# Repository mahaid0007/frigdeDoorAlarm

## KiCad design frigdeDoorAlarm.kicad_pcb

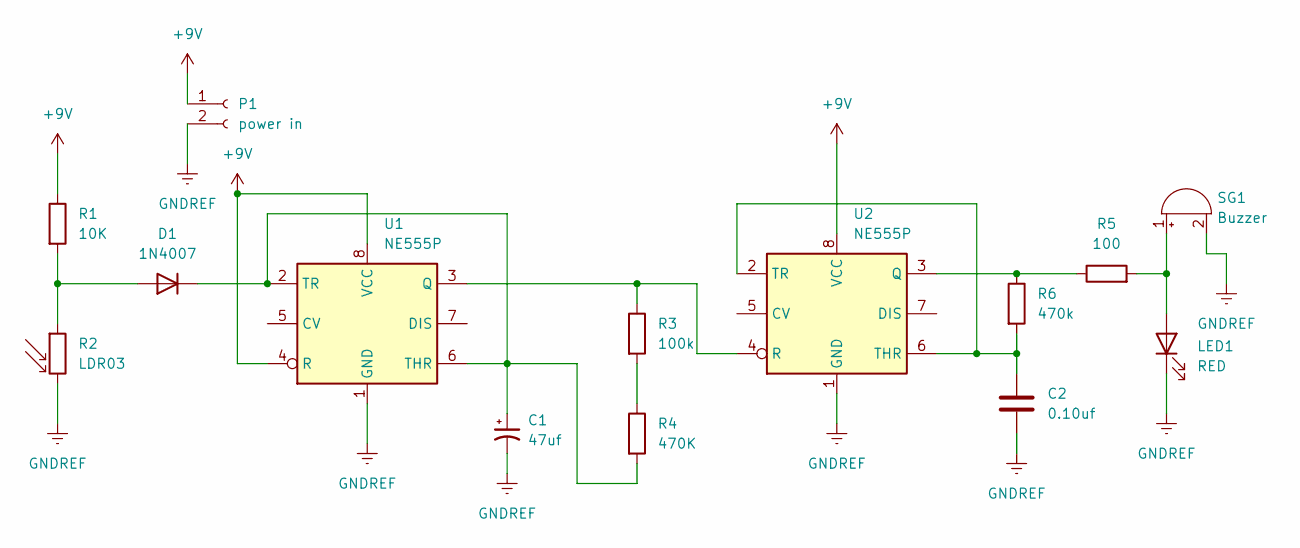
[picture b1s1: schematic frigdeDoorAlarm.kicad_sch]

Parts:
C1: 47uf; CP_Radial_D4.0mm_P1.50mm
C2: 0.10uf; C_Radial_D4.0mm_H5.0mm_P1.50mm
D1: 1N4007; D_A-405_P10.16mm_Horizontal
LED1: RED; LED_D3.0mm
P1: power in; JWT_A3963_1x02_P3.96mm_Vertical
R1: 10K; R_Axial_DIN0207_L6.3mm_D2.5mm_P7.62mm_Horizontal
R2: LDR03; R_LDR_10x8.5mm_P7.6mm_Vertical
R3: 100k; R_Axial_DIN0207_L6.3mm_D2.5mm_P7.62mm_Horizontal
R4: 470K; R_Axial_DIN0207_L6.3mm_D2.5mm_P7.62mm_Horizontal
R5: 100; R_Axial_DIN0207_L6.3mm_D2.5mm_P7.62mm_Horizontal
R6: 470k; R_Axial_DIN0207_L6.3mm_D2.5mm_P7.62mm_Horizontal
SG1: Buzzer; Buzzer_D14mm_H7mm_P10mm
U1, U2: NE555P; DIP-8_W7.62mm

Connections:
+9V: P1.1, R1.1, U1.4 (R), U1.8 (VCC), U2.8 (VCC)
GNDREF: C1.2, C2.2, LED1.1 (K), P1.2, R2.2, SG1.2 (+), U1.1 (GND), U2.1 (GND)
unnamed: C1.1, D1.1 (K), R4.2, U1.2 (TR), U1.6 (THR)
unnamed: C2.1, R6.2, U2.2 (TR), U2.6 (THR)
unnamed: D1.2 (A), R1.2, R2.1
unnamed: LED1.2 (A), R5.2, SG1.1 (-)
unnamed: R3.1, U1.3 (Q), U2.4 (R)
unnamed: R3.2, R4.1
unnamed: R5.1, R6.1, U2.3 (Q)

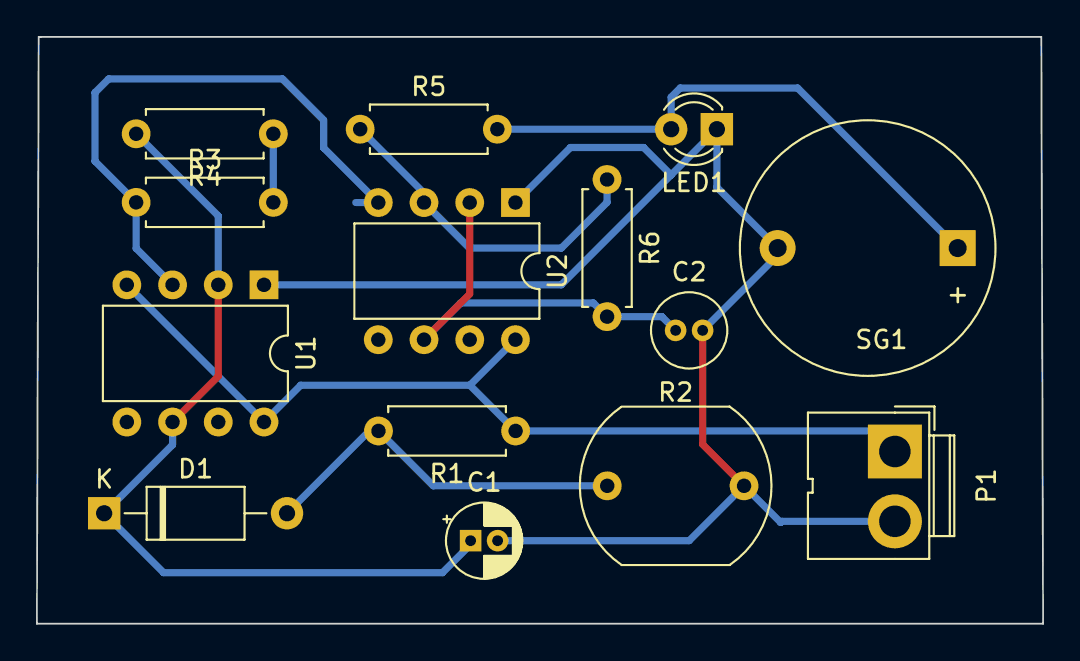
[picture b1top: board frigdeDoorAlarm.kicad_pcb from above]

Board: 2 copper layers, 55.9 x 32.6 mm, 14 parts (0 on the bottom side), 9 nets.

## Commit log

2023-03-22 a simple pcb i designed to learn kicad
